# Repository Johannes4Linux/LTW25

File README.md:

# Linux Treiber Workshop 2025

This repository contains the material for my Linux Driver Workshop 2025:

- PCB Schematic and Layout for RGB LED PCB
- Repositories with Workshop at specific Events as submodules
    - Workshop at Chemnitzer Linux Tagen

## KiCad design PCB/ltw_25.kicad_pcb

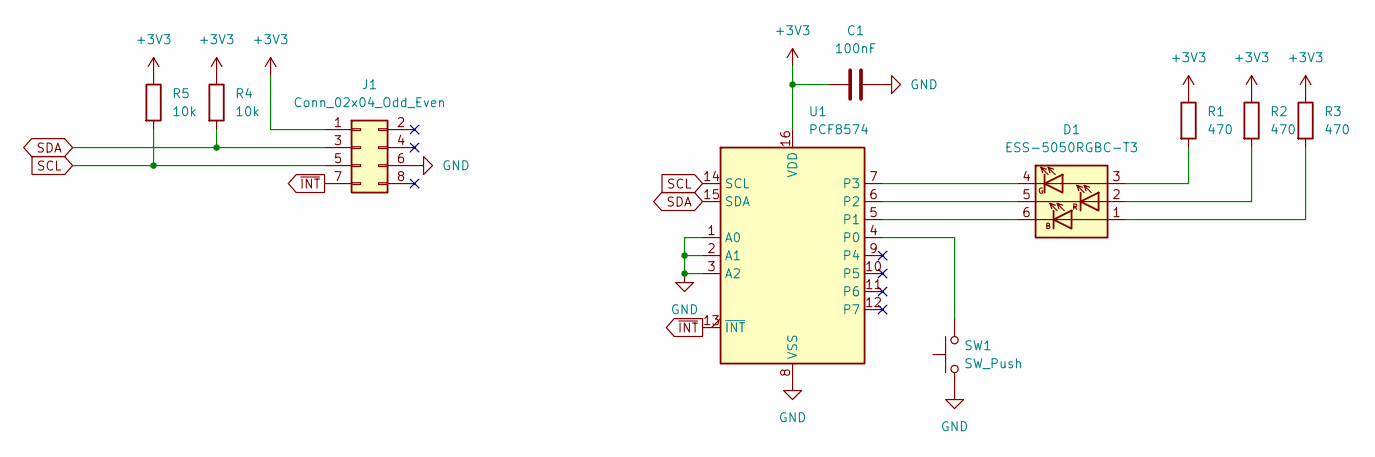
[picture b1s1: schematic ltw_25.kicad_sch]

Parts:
C1: 100nF; C_0603_1608Metric_Pad1.08x0.95mm_HandSolder
D1: ESS-5050RGBC-T3; LED_RGB_5050-6
J1: Conn_02x04_Odd_Even; PinSocket_2x04_P2.54mm_Vertical
R1, R2, R3: 470; R_0603_1608Metric_Pad0.98x0.95mm_HandSolder
R4, R5: 10k; R_0603_1608Metric_Pad0.98x0.95mm_HandSolder
SW1: SW_Push; SW_SPST_PTS645
U1: PCF8574; SOIC-16W_7.5x10.3mm_P1.27mm

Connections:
+3V3: C1.1, J1.1, R1.1, R2.1, R3.1, R4.1, R5.1, U1.16 (VDD)
GND: C1.2, J1.6, SW1.1, U1.1 (A0), U1.2 (A1), U1.3 (A2), U1.8 (VSS)
unnamed: D1.6 (AB), U1.5 (P1)
unnamed: D1.5 (AG), U1.6 (P2)
unnamed: D1.4 (AR), U1.7 (P3)
unnamed: D1.1 (KB), R3.2
unnamed: D1.2 (KG), R2.2
unnamed: D1.3 (KR), R1.2
unnamed: SW1.2, U1.4 (P0)
SCL: J1.5, R5.2, U1.14 (SCL)
SDA: J1.3, R4.2, U1.15 (SDA)
~INT: J1.7, U1.13 (~INT)

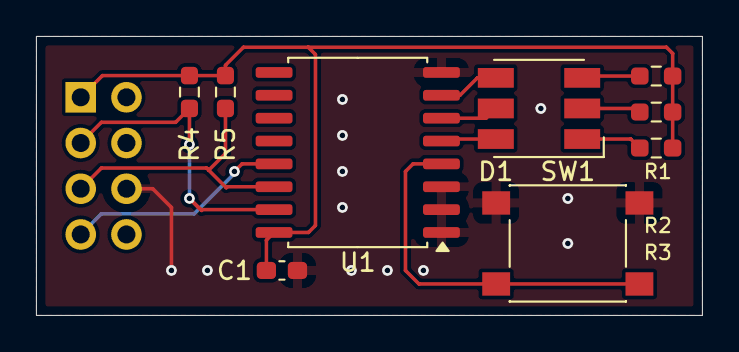
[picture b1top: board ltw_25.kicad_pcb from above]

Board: 2 copper layers, 37.0 x 15.5 mm, 10 parts (1 on the bottom side), 12 nets.

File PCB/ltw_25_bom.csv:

"ID";"Bezeichner";"Footprint";"Stückzahl";"Bezeichnung";"Anbieter und Referenz";
1;"D1";"LED_RGB_5050-6";1;"ESS-5050RGBC-T3";;;
2;"R2,R1,R3";"R_0603_1608Metric_Pad0.98x0.95mm_HandSolder";3;"470";;;
3;"R5,R4";"R_0603_1608Metric_Pad0.98x0.95mm_HandSolder";2;"10k";;;
4;"SW1";"SW_SPST_PTS645";1;"SW_Push";;;
5;"U1";"SOIC-16W_7.5x10.3mm_P1.27mm";1;"PCF8574";;;
6;"C1";"C_0603_1608Metric_Pad1.08x0.95mm_HandSolder";1;"100nF";;;
7;"J1";"PinSocket_2x04_P2.54mm_Vertical";1;"Conn_02x04_Odd_Even";;;

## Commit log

2025-02-28 Upload PCB design
2025-03-16 Upload Slides for presentation and code snippets from slides
2025-03-17 Update slides
2025-03-22 Added submodule for CLT and moved stuff there
2025-03-22 Updated Submodule
2025-03-23 Update in submodule
2025-03-30 Added BOM and schematic as PDF
2025-08-09 Added files of LUGA LIT and FrOSCon
